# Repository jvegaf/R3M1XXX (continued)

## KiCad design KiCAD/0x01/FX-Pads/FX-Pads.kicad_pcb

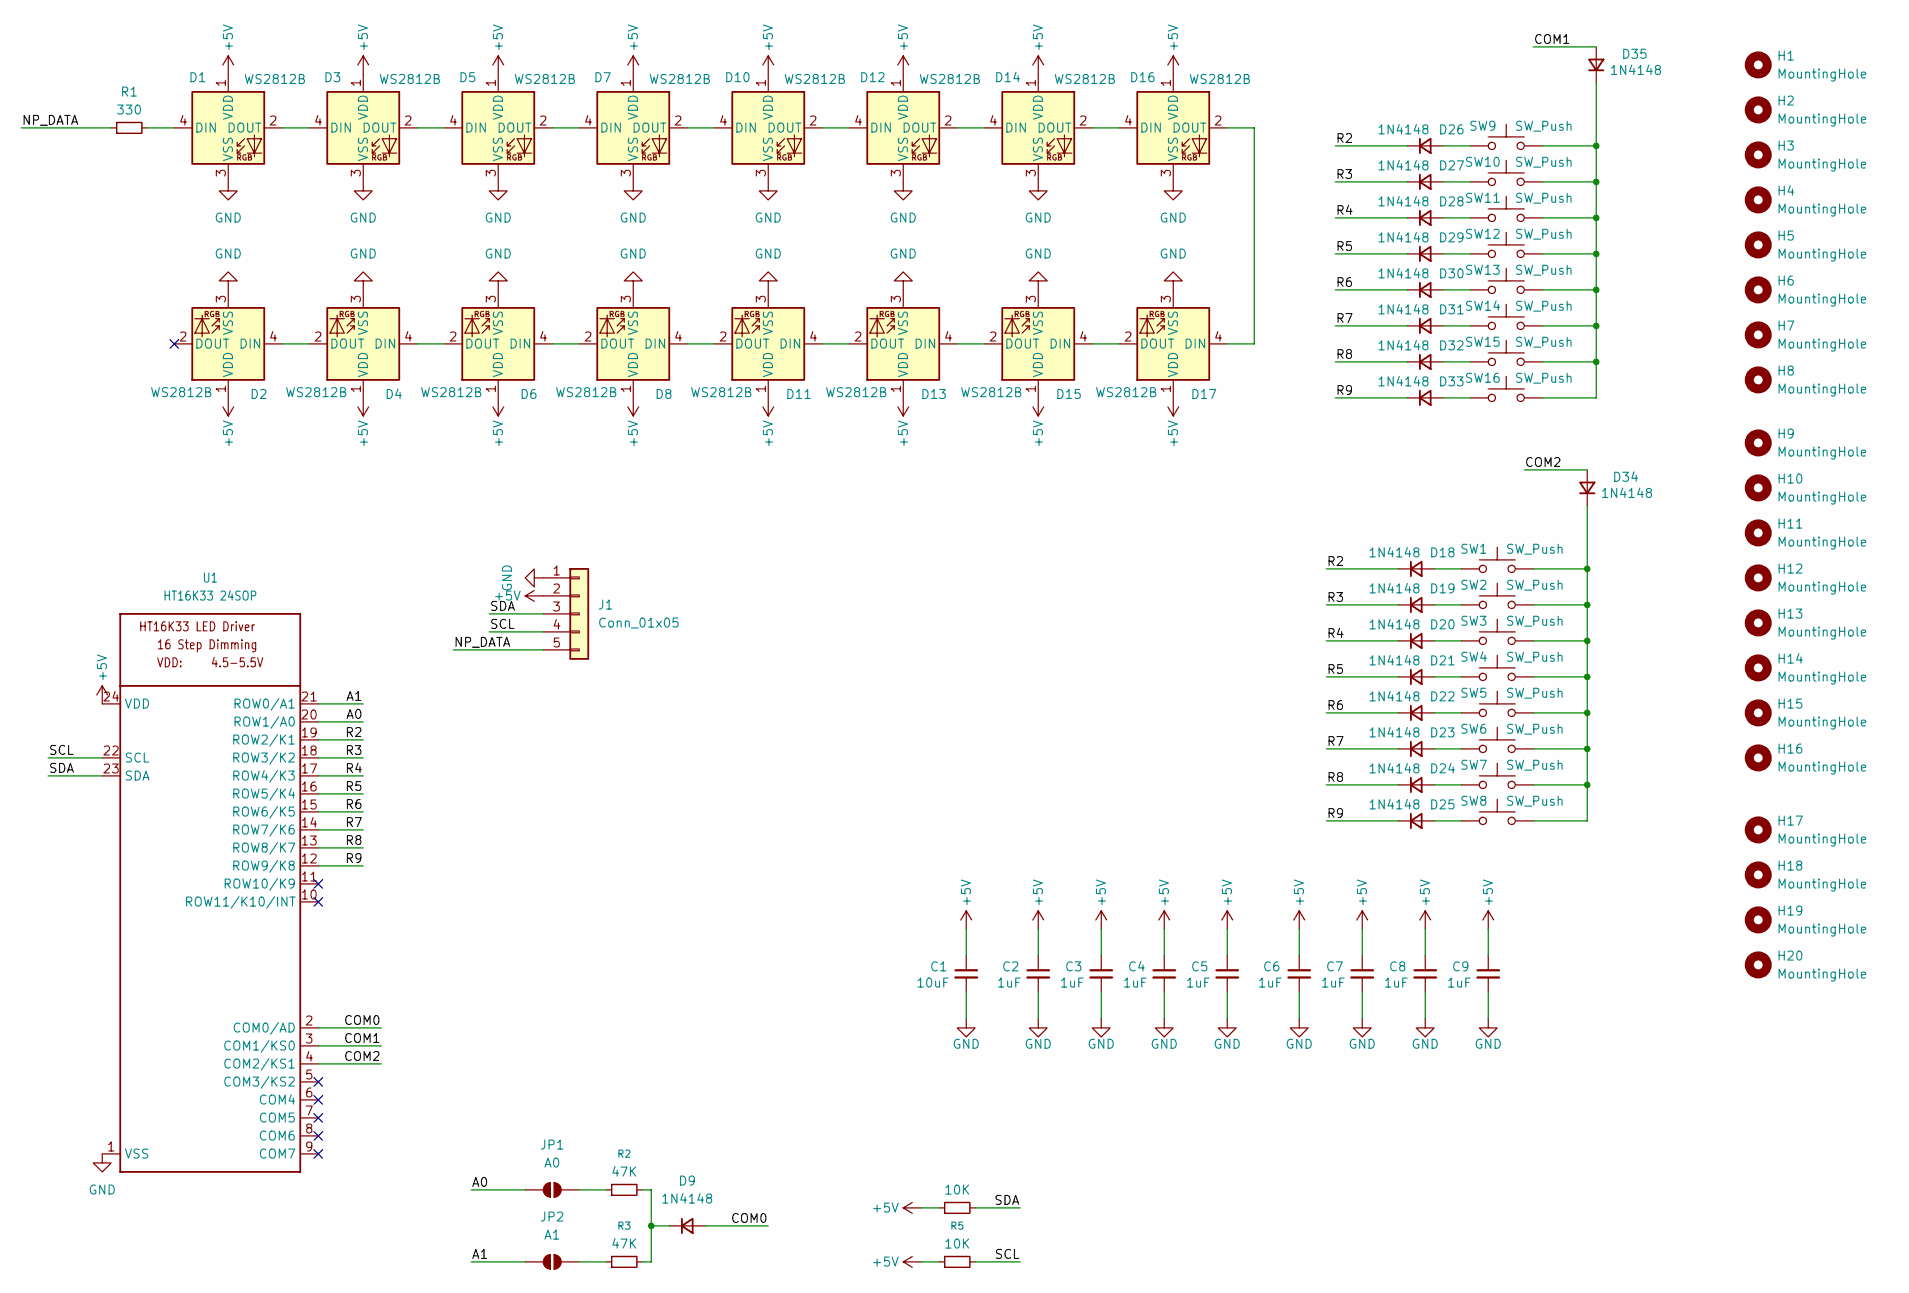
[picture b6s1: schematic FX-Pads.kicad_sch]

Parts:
C1: 10uF; C_0805_2012Metric_Pad1.18x1.45mm_HandSolder
C2, C3, C4, C5, C6, C7, C8, C9: 1uF; C_0603_1608Metric_Pad1.08x0.95mm_HandSolder
D1, D2, D3, D4, D5, D6, D7, D8, D10, D11, D12, D13, D14, D15, D16, D17: WS2812B; LED_WS2812B_PLCC4_5.0x5.0mm_P3.2mm
D9, D18, D19, D20, D21, D22, D23, D24, D25, D26, D27, D28, D29, D30, D31, D32, D33, D34, D35: 1N4148; D_SOD-123
H1, H2, H3, H4, H5, H6, H7, H8, H9, H10, H11, H12, H13, H14, H15, H16: MountingHole; MountingHole_3.2mm_M3_ISO7380
H17, H18, H19, H20: MountingHole; MountingHole_2.2mm_M2
J1: Conn_01x05; JST_PH_S5B-PH-K_1x05_P2.00mm_Horizontal
JP1: A0; SolderJumper-2_P1.3mm_Open_RoundedPad1.0x1.5mm
JP2: A1; SolderJumper-2_P1.3mm_Open_RoundedPad1.0x1.5mm
R1: 330; R_0805_2012Metric_Pad1.20x1.40mm_HandSolder
R2, R3: 47K; R_0805_2012Metric_Pad1.20x1.40mm_HandSolder
R4, R5: 10K; R_0805_2012Metric_Pad1.20x1.40mm_HandSolder
SW1, SW2, SW3, SW4, SW5, SW6, SW7, SW8, SW9, SW10, SW11, SW12, SW13, SW14, SW15, SW16: SW_Push; sw-pad
U1: HT16K33 24SOP; SOIC-24W_7.5x15.4mm_P1.27mm

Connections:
+5V: C1.1, C2.1, C3.1, C4.1, C5.1, C6.1, C7.1, C8.1, C9.1, D1.1 (VDD), D2.1 (VDD), D3.1 (VDD), D4.1 (VDD), D5.1 (VDD), D6.1 (VDD), D7.1 (VDD), D8.1 (VDD), D10.1 (VDD), D11.1 (VDD), D12.1 (VDD), D13.1 (VDD), D14.1 (VDD), D15.1 (VDD), D16.1 (VDD), D17.1 (VDD), J1.2, R4.1, R5.1, U1.24 (VDD)
/A0: JP1.1 (A), U1.20 (ROW1/A0)
/A1: JP2.1 (A), U1.21 (ROW0/A1)
/COM0: D9.2 (A), U1.2 (COM0/AD)
/COM1: D35.2 (A), U1.3 (COM1/KS0)
/COM2: D34.2 (A), U1.4 (COM2/KS1)
/NP_DATA: J1.5, R1.1
/R2: D18.1 (K), D26.1 (K), U1.19 (ROW2/K1)
/R3: D19.1 (K), D27.1 (K), U1.18 (ROW3/K2)
/R4: D20.1 (K), D28.1 (K), U1.17 (ROW4/K3)
/R5: D21.1 (K), D29.1 (K), U1.16 (ROW5/K4)
/R6: D22.1 (K), D30.1 (K), U1.15 (ROW6/K5)
/R7: D23.1 (K), D31.1 (K), U1.14 (ROW7/K6)
/R8: D24.1 (K), D32.1 (K), U1.13 (ROW8/K7)
/R9: D25.1 (K), D33.1 (K), U1.12 (ROW9/K8)
/SCL: J1.4, R5.2, U1.22 (SCL)
/SDA: J1.3, R4.2, U1.23 (SDA)
GND: C1.2, C2.2, C3.2, C4.2, C5.2, C6.2, C7.2, C8.2, C9.2, D1.3 (VSS), D2.3 (VSS), D3.3 (VSS), D4.3 (VSS), D5.3 (VSS), D6.3 (VSS), D7.3 (VSS), D8.3 (VSS), D10.3 (VSS), D11.3 (VSS), D12.3 (VSS), D13.3 (VSS), D14.3 (VSS), D15.3 (VSS), D16.3 (VSS), D17.3 (VSS), J1.1, U1.1 (VSS)
unnamed: D1.4 (DIN), R1.2
unnamed: D1.2 (DOUT), D3.4 (DIN)
unnamed: D2.4 (DIN), D4.2 (DOUT)
unnamed: D3.2 (DOUT), D5.4 (DIN)
unnamed: D4.4 (DIN), D6.2 (DOUT)
unnamed: D5.2 (DOUT), D7.4 (DIN)
unnamed: D6.4 (DIN), D8.2 (DOUT)
unnamed: D9.1 (K), R2.2, R3.2
unnamed: D7.2 (DOUT), D10.4 (DIN)
unnamed: D10.2 (DOUT), D12.4 (DIN)
unnamed: D11.4 (DIN), D13.2 (DOUT)
unnamed: D8.4 (DIN), D11.2 (DOUT)
unnamed: D12.2 (DOUT), D14.4 (DIN)
unnamed: D13.4 (DIN), D15.2 (DOUT)
unnamed: D14.2 (DOUT), D16.4 (DIN)
unnamed: D15.4 (DIN), D17.2 (DOUT)
unnamed: D16.2 (DOUT), D17.4 (DIN)
unnamed: D18.2 (A), SW1.1
unnamed: D19.2 (A), SW2.1
unnamed: D20.2 (A), SW3.1
unnamed: D21.2 (A), SW4.1
unnamed: D22.2 (A), SW5.1
unnamed: D23.2 (A), SW6.1
unnamed: D24.2 (A), SW7.1
unnamed: D25.2 (A), SW8.1
unnamed: D26.2 (A), SW9.1
unnamed: D27.2 (A), SW10.1
unnamed: D28.2 (A), SW11.1
unnamed: D29.2 (A), SW12.1
unnamed: D30.2 (A), SW13.1
unnamed: D31.2 (A), SW14.1
unnamed: D32.2 (A), SW15.1
unnamed: D33.2 (A), SW16.1
unnamed: D34.1 (K), SW1.2, SW2.2, SW3.2, SW4.2, SW5.2, SW6.2, SW7.2, SW8.2
unnamed: D35.1 (K), SW9.2, SW10.2, SW11.2, SW12.2, SW13.2, SW14.2, SW15.2, SW16.2
unnamed: JP1.2 (B), R2.1
unnamed: JP2.2 (B), R3.1

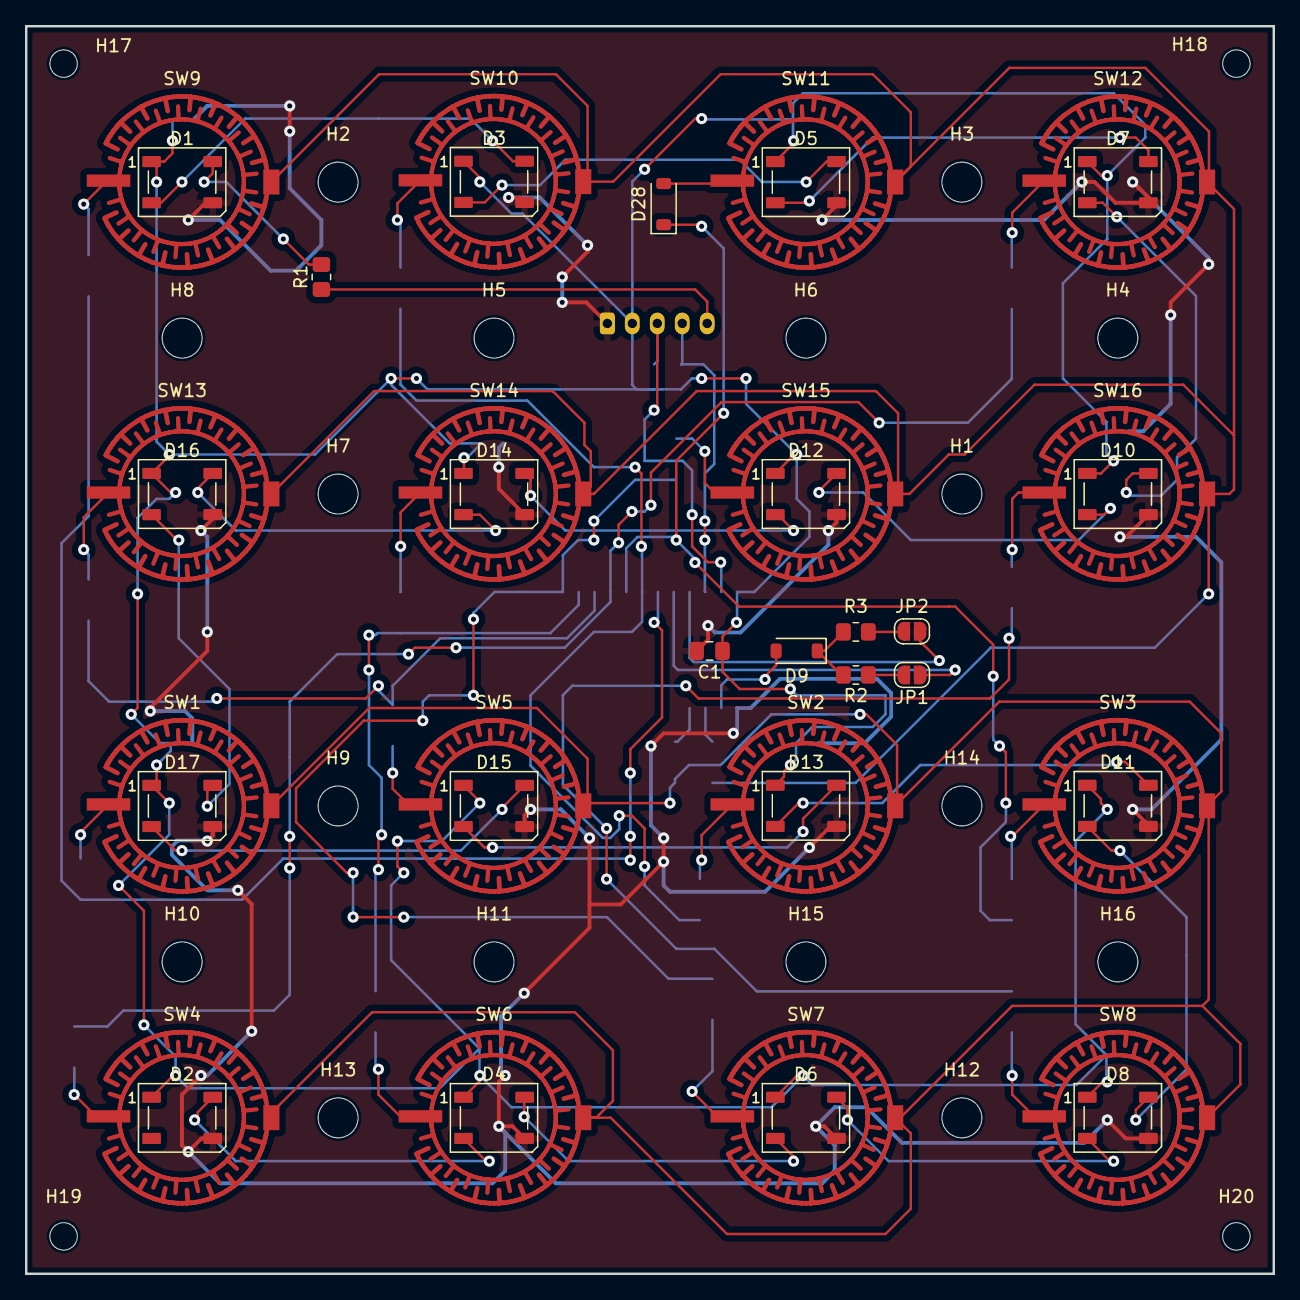
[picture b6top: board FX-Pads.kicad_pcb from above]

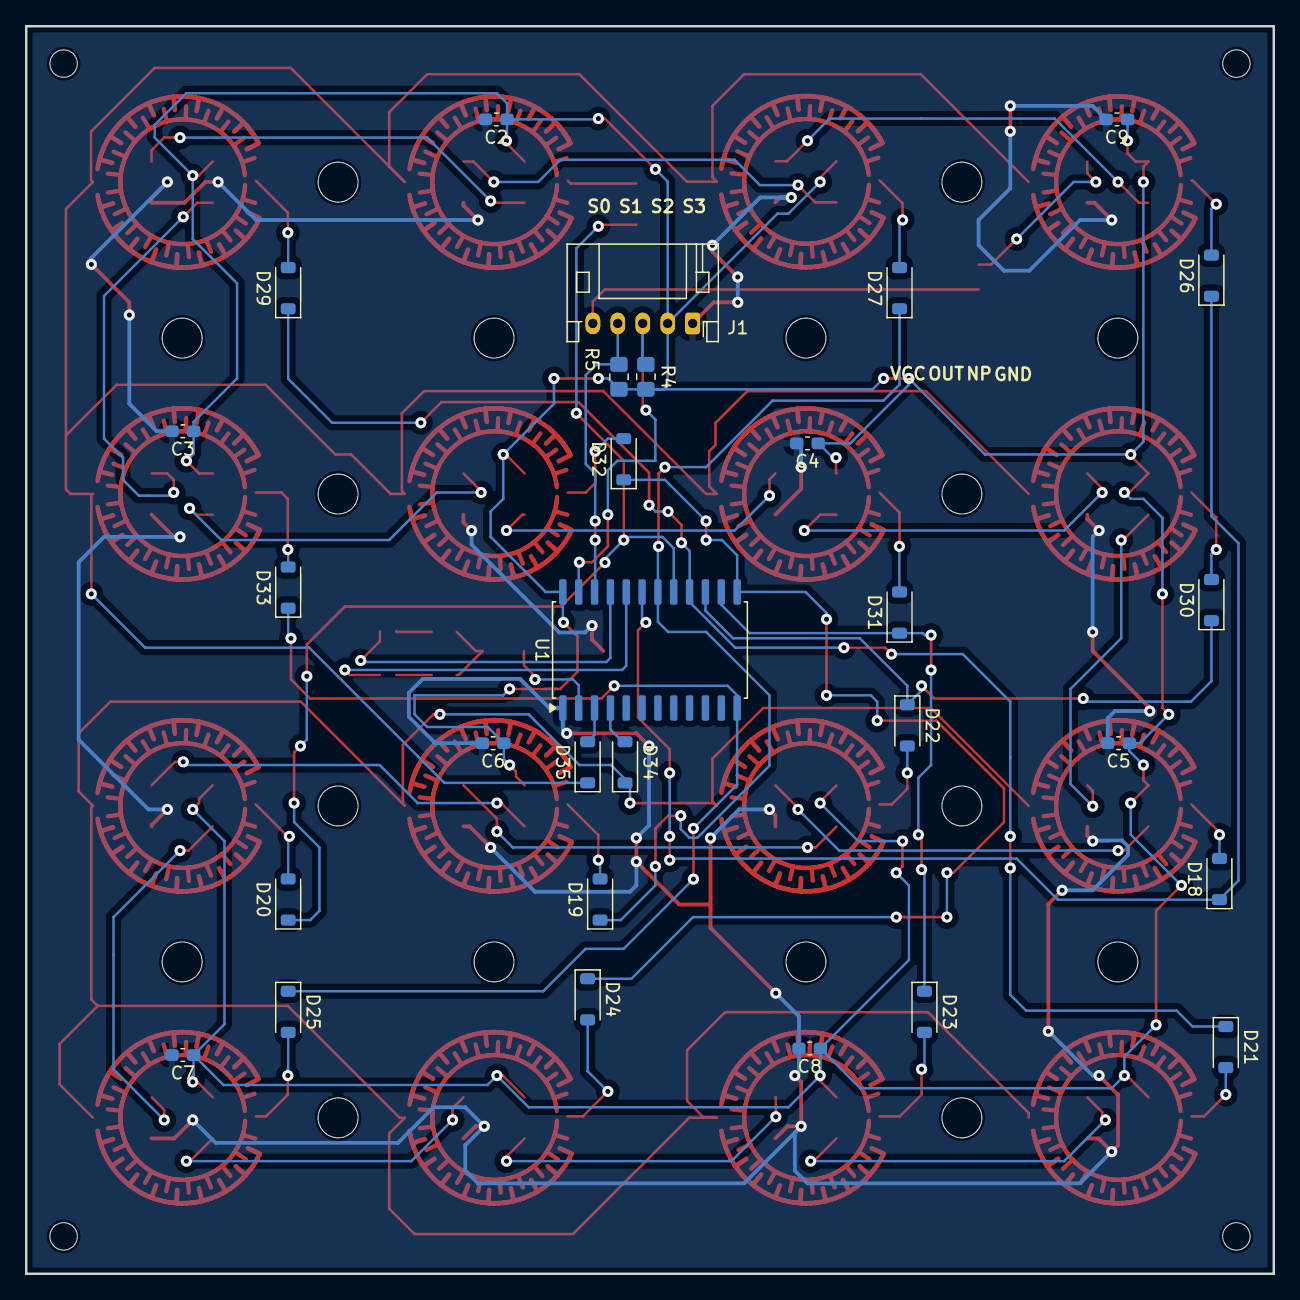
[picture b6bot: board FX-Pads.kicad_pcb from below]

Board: 2 copper layers, 100.0 x 100.0 mm, 89 parts (29 on the bottom side), 55 nets.

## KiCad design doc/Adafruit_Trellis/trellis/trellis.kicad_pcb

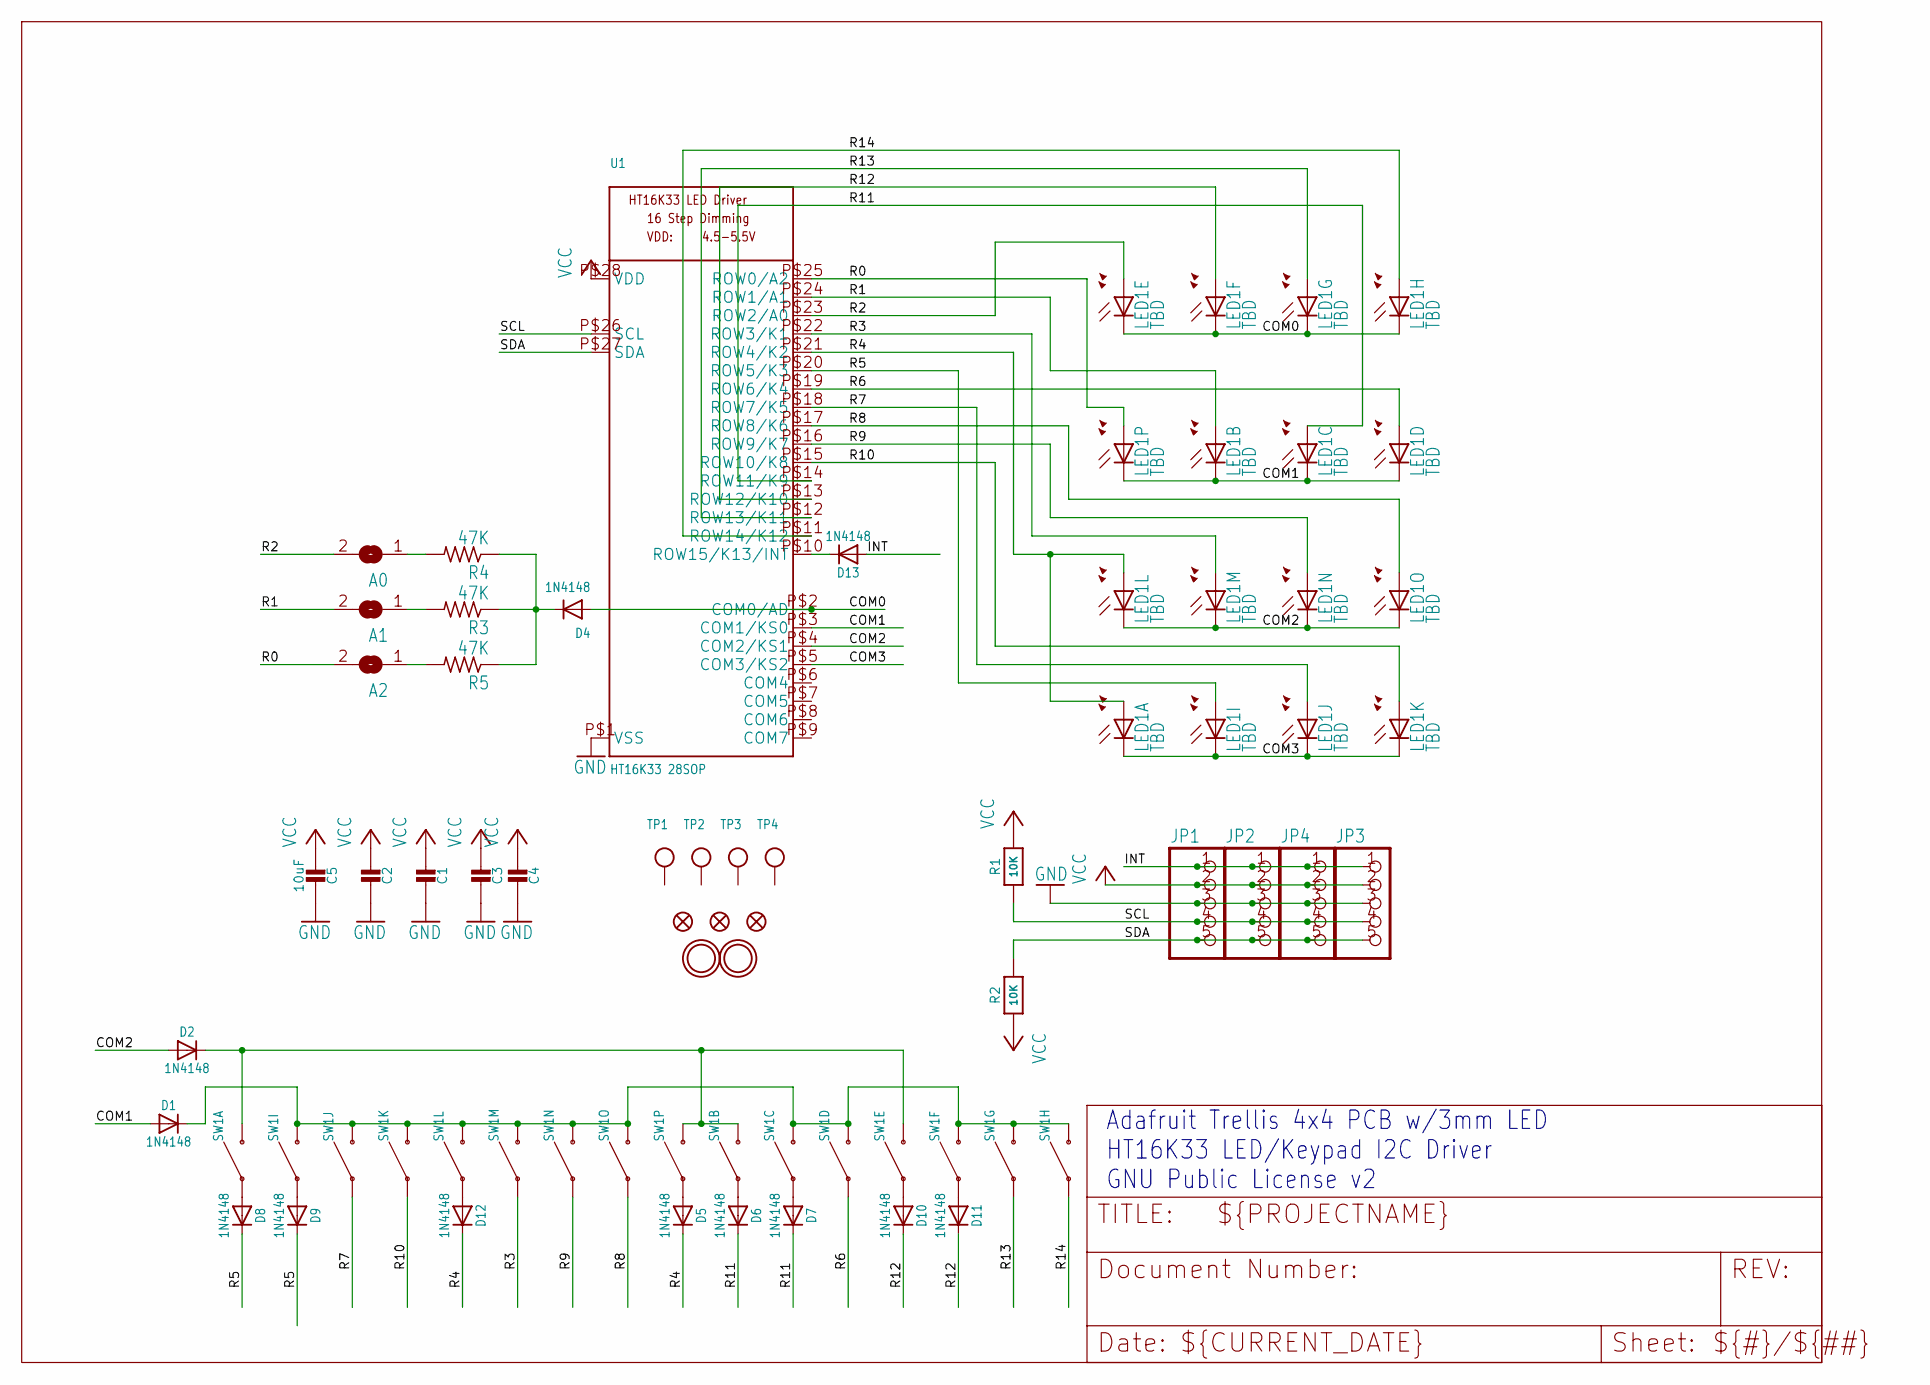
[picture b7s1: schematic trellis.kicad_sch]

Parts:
A0, A1, A2: SOLDERJUMPERREFLOW_NOPASTE; SOLDERJUMPER_REFLOW_NOPASTE
C1, C2, C3, C4: CAP_CERAMIC_0805; _0805
C5: 10uF; _0805
D1, D2, D5, D6, D7, D8, D9, D10, D11, D12, D13: 1N4148; SOD-323
D4: 1N4148; SOD-323F
FID1, FID2, FID3: FIDUCIAL""; FIDUCIAL_1MM
JP1, JP2, JP3, JP4: HEADER-1X5EDGESMT; 1X5_SMT
LED1: TBD; LED3MM-4X4GRID
R1, R2: 10K; _0805
R3, R4, R5: 47K; R0805
SW1: SWITCH-SILICON-4X4GRID-10MM-5.4MM; ELAST_PAD_SQUARE_10MM_5.4MM_4X4GRID
TP1, TP2, TP3, TP4: TESTPOINT; TESTPOINT_SMT
U1: HT16K33 28SOP; SOP28_300MIL
U$1, U$2: MOUNTINGHOLE2.5; MOUNTINGHOLE_2.5_PLATED

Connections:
COM0: D4.A, LED1.K13 (C), LED1.K14 (C), LED1.K15 (C), LED1.K16 (C), U1.P$2 (COM0/AD)
COM1: D1.A, LED1.K9 (C), LED1.K10 (C), LED1.K11 (C), LED1.K12 (C), U1.P$3 (COM1/KS0)
COM2: D2.A, LED1.K5 (C), LED1.K6 (C), LED1.K7 (C), LED1.K8 (C), U1.P$4 (COM2/KS1)
COM3: LED1.K1 (C), LED1.K2 (C), LED1.K3 (C), LED1.K4 (C), U1.P$5 (COM3/KS2)
GND: C1.1, C2.1, C3.1, C4.1, C5.1, JP1.3, JP2.3, JP3.3, JP4.3, U1.P$1 (VSS)
INT: D13.A, JP1.1, JP2.1, JP3.1, JP4.1
unnamed: D2.C, SW1.B1, SW1.B9, SW1.B10, SW1.B13
unnamed: D13.C, U1.P$10 (ROW15/K13/INT)
unnamed: D5.A, SW1.A9
unnamed: D6.A, SW1.A10
unnamed: D1.C, SW1.B2, SW1.B3, SW1.B4, SW1.B5, SW1.B6, SW1.B7, SW1.B8, SW1.B11, SW1.B12, SW1.B14, SW1.B15, SW1.B16
unnamed: D7.A, SW1.A11
unnamed: D8.A, SW1.A1
unnamed: D9.A, SW1.A2
unnamed: A2.1, R5.2
unnamed: D10.A, SW1.A13
unnamed: D11.A, SW1.A14
unnamed: D12.A, SW1.A5
unnamed: D4.C, R3.1, R4.1, R5.1
unnamed: A1.1, R3.2
unnamed: A0.1, R4.2
R0: A2.2, LED1.A9 (A), U1.P$25 (ROW0/A2)
R1: A1.2, LED1.A10 (A), U1.P$24 (ROW1/A1)
R2: A0.2, LED1.A13 (A), U1.P$23 (ROW2/A0)
R3: LED1.A6 (A), SW1.A6, U1.P$22 (ROW3/K1)
R4: D5.C, D12.C, LED1.A1 (A), LED1.A5 (A), U1.P$21 (ROW4/K2)
R5: D8.C, D9.C, LED1.A2 (A), U1.P$20 (ROW5/K3)
R6: LED1.A12 (A), SW1.A12, U1.P$19 (ROW6/K4)
R7: LED1.A3 (A), SW1.A3, U1.P$18 (ROW7/K5)
R8: LED1.A8 (A), SW1.A8, U1.P$17 (ROW8/K6)
R9: LED1.A7 (A), SW1.A7, U1.P$16 (ROW9/K7)
R10: LED1.A4 (A), SW1.A4, U1.P$15 (ROW10/K8)
R11: D6.C, D7.C, LED1.A11 (A), U1.P$14 (ROW11/K9)
R12: D10.C, D11.C, LED1.A14 (A), U1.P$13 (ROW12/K10)
R13: LED1.A15 (A), SW1.A15, U1.P$12 (ROW13/K11)
R14: LED1.A16 (A), SW1.A16, U1.P$11 (ROW14/K12)
SCL: JP1.4, JP2.4, JP3.4, JP4.4, R1.1, U1.P$26 (SCL)
SDA: JP1.5, JP2.5, JP3.5, JP4.5, R2.2, U1.P$27 (SDA)
VCC: C1.2, C2.2, C3.2, C4.2, C5.2, JP1.2, JP2.2, JP3.2, JP4.2, R1.2, R2.1, U1.P$28 (VDD)

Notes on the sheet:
Adafruit Trellis 4x4 PCB w/3mm LED HT16K33 LED/Keypad I2C Driver GNU Public License v2

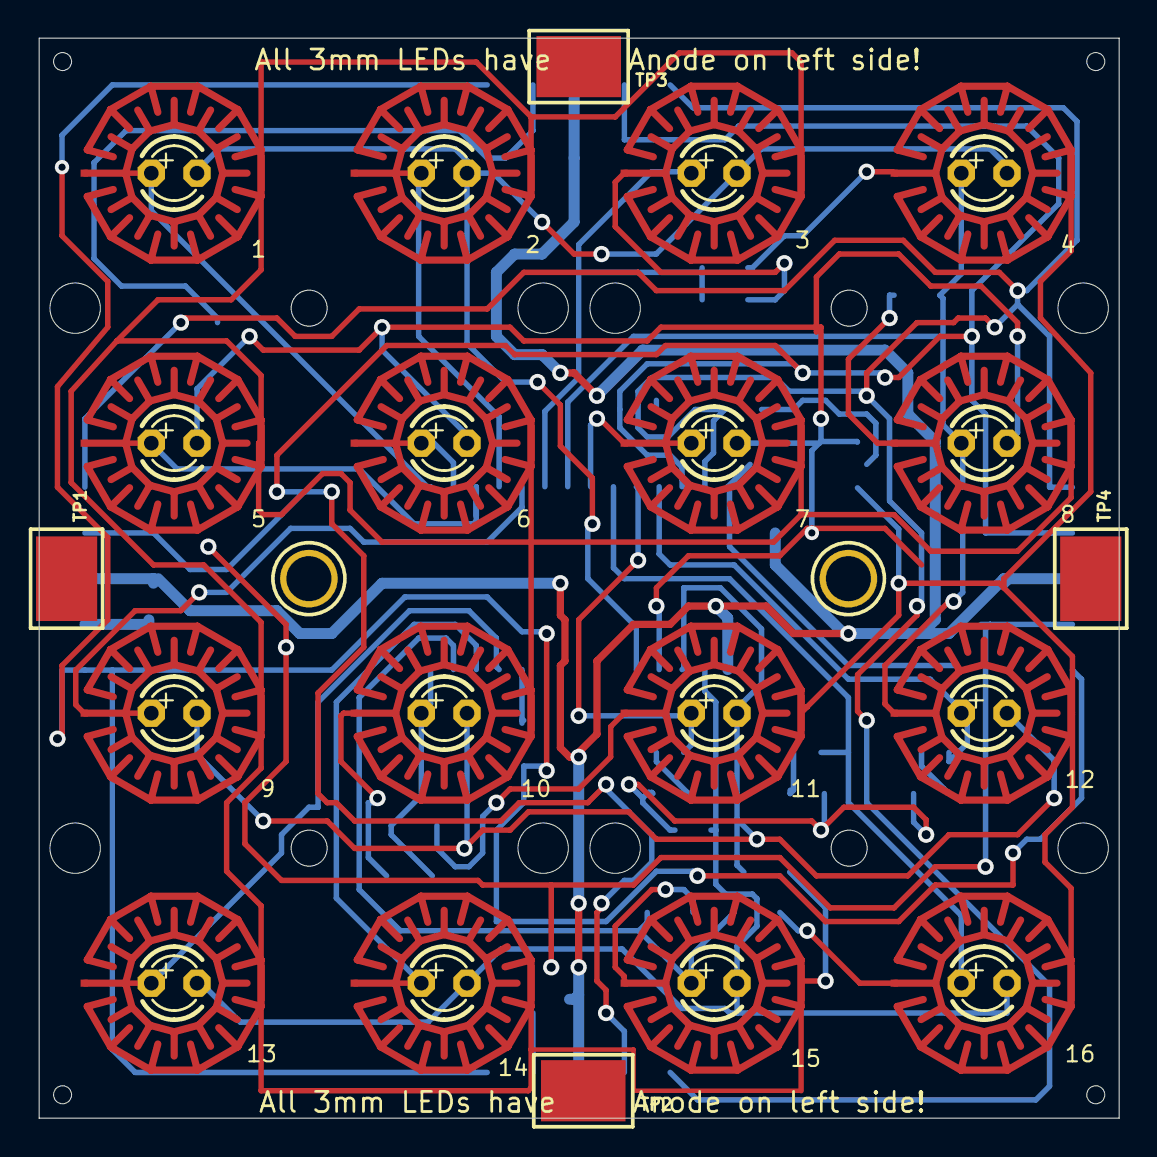
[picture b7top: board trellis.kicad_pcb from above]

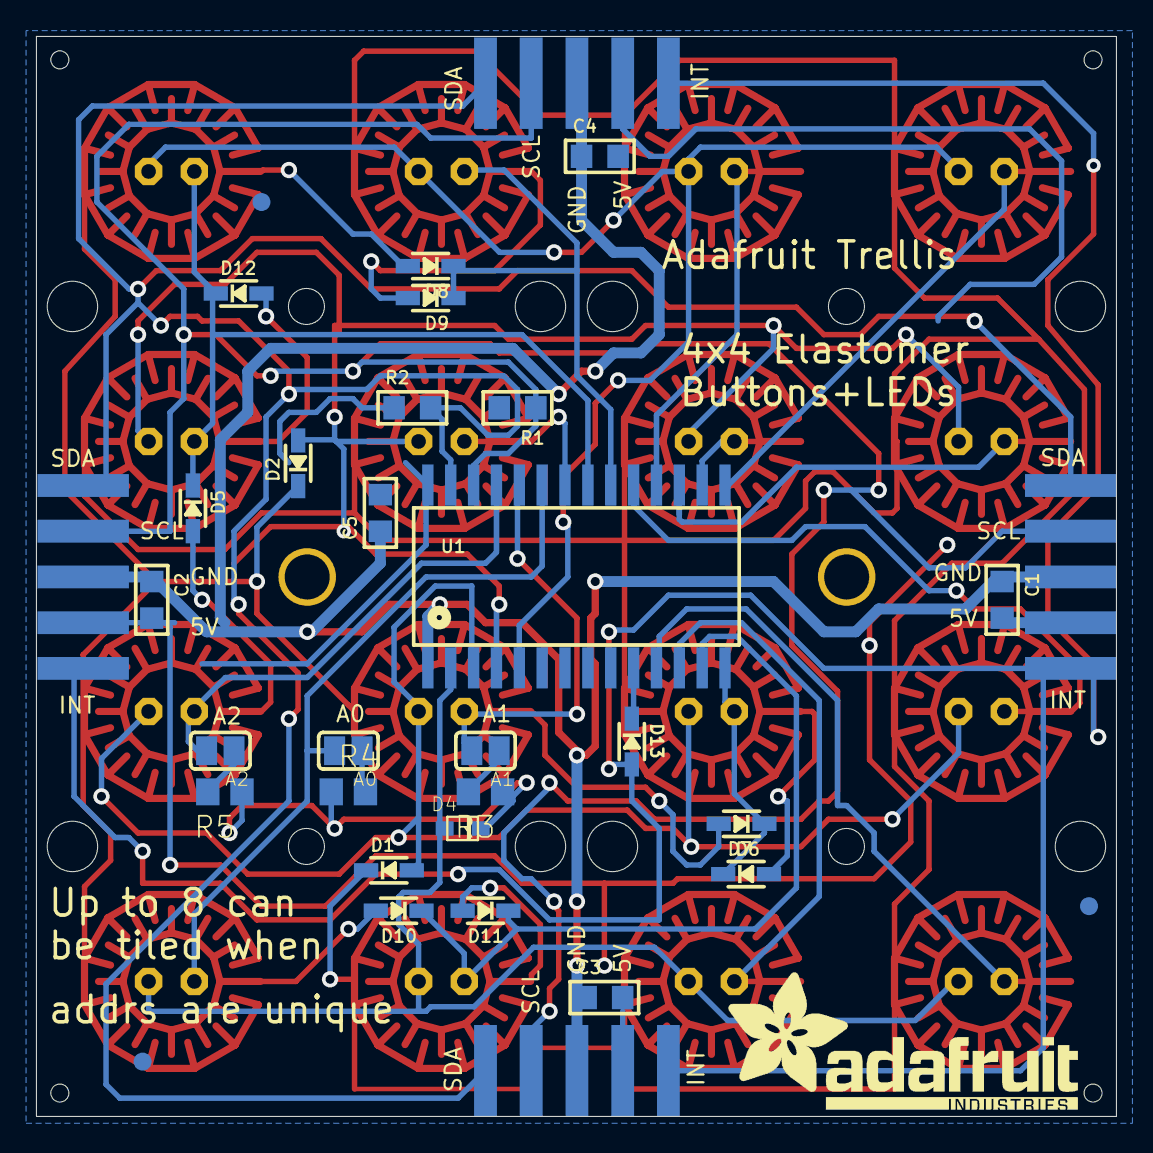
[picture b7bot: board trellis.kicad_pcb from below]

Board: 2 copper layers, 60.0 x 60.0 mm, 42 parts (34 on the bottom side), 39 nets.

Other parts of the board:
U$3: ADAFRUIT_TEXT_20MM

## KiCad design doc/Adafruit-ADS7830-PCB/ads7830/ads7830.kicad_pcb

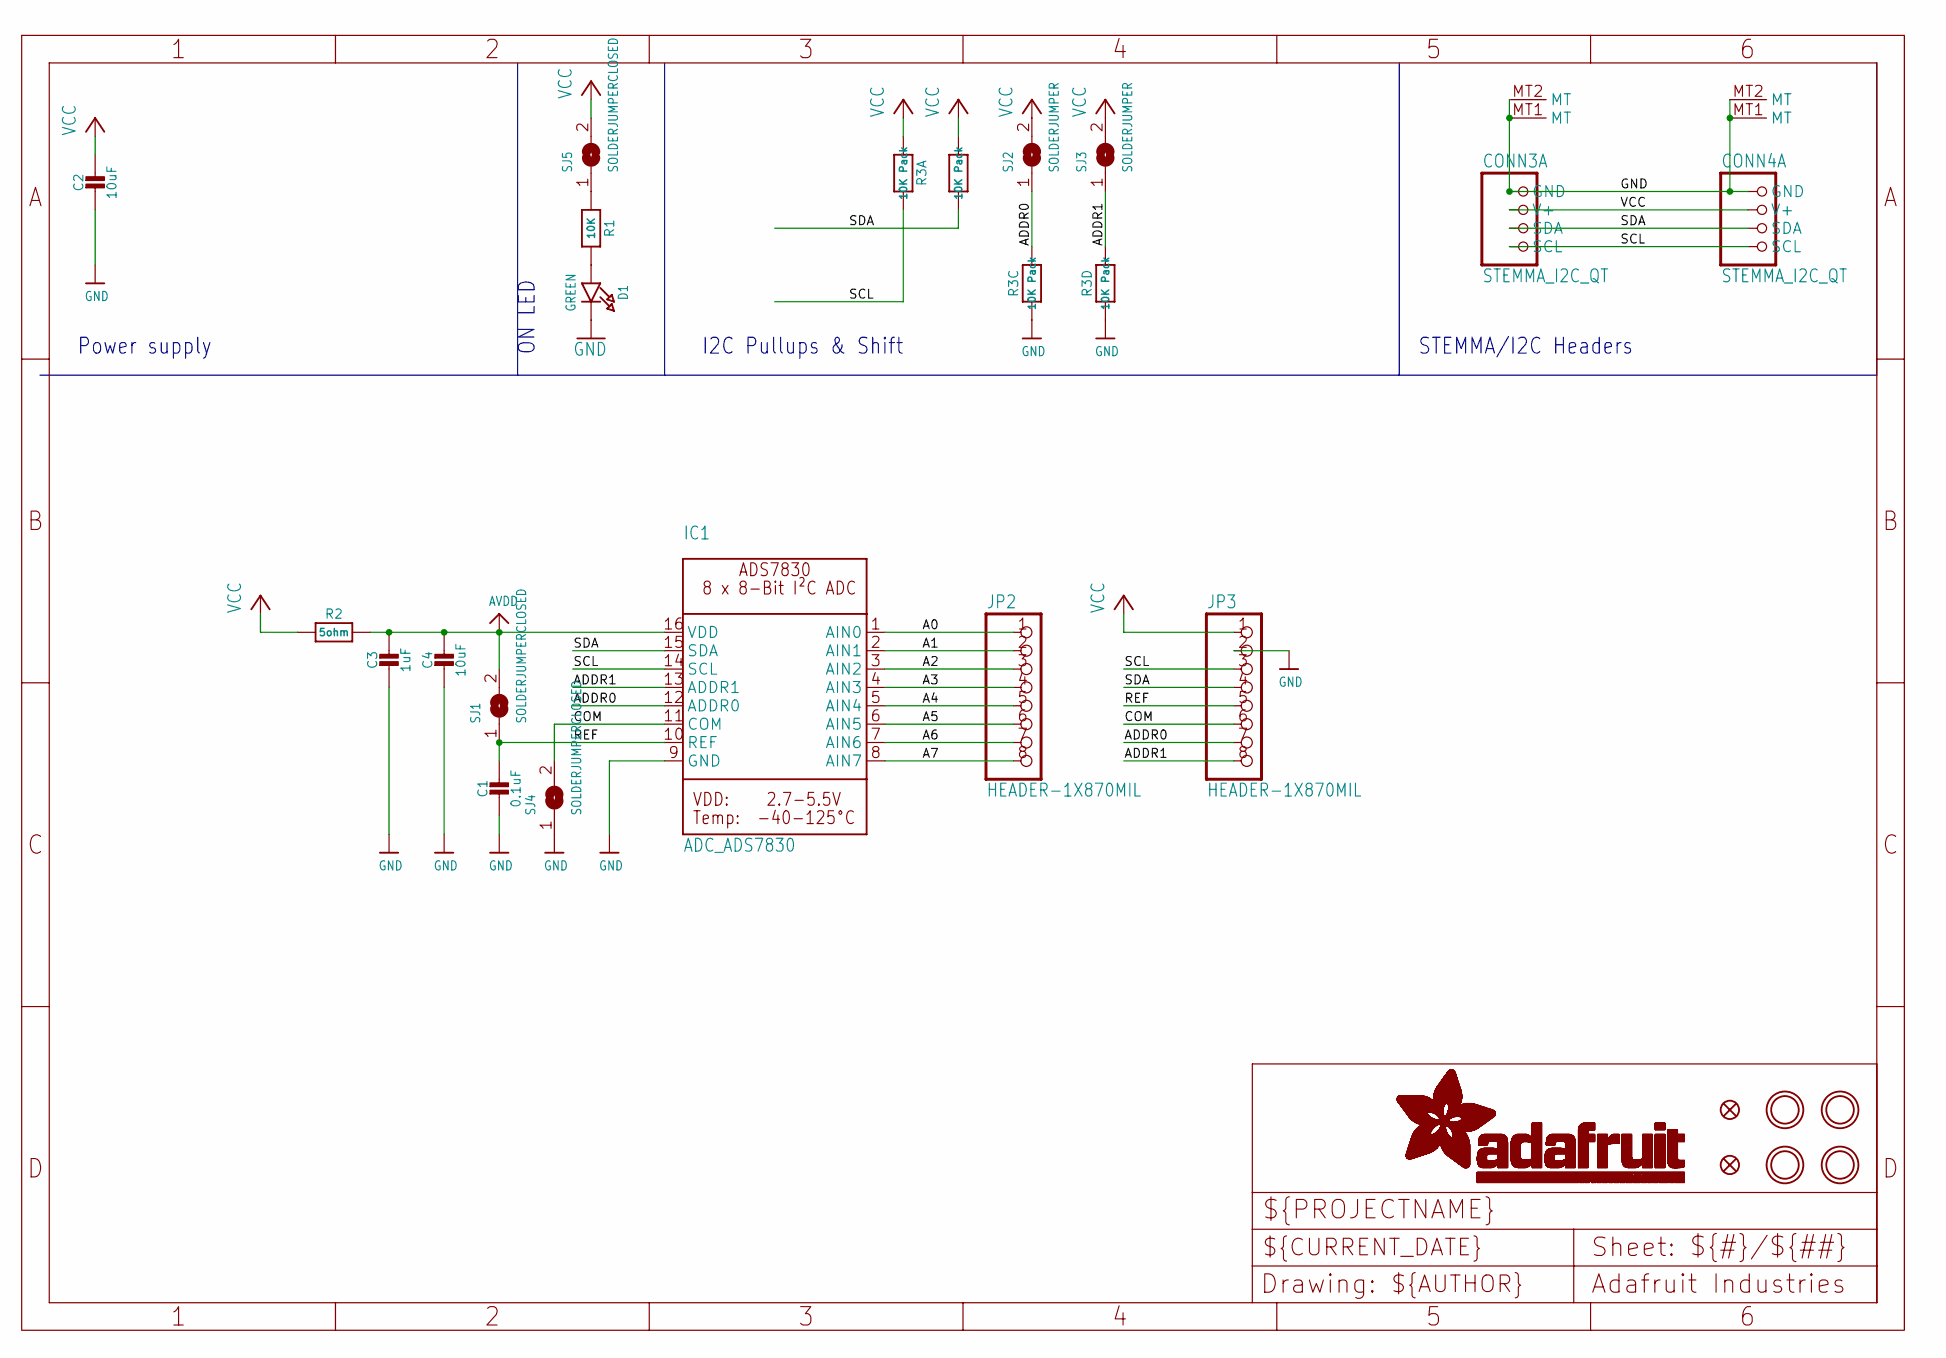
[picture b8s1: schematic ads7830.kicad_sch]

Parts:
C1: 0.1uF; 0603-NO
C2, C4: 10uF; 0805-NO
C3: 1uF; 0603-NO
CONN3, CONN4: STEMMA_I2C_QT; JST_SH4
D1: GREEN; CHIPLED_0603_NOOUTLINE
FID3, FID4: FIDUCIAL_1MM
IC1: ADC_ADS7830; TSSOP16
JP2, JP3: HEADER-1X870MIL; 1X08_ROUND_70
R1: 10K; 0603-NO
R2: 5ohm; 0603-NO
R3: 10K Pack; RESPACK_4X0603
SJ1, SJ4, SJ5: SOLDERJUMPERCLOSED; SOLDERJUMPER_CLOSEDWIRE
SJ2, SJ3: SOLDERJUMPER; SOLDERJUMPER_ARROW_NOPASTE
U$1, U$17, U$19, U$21: MOUNTINGHOLE2.5; MOUNTINGHOLE_2.5_PLATED

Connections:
A0: IC1.1 (AIN0), JP2.1
A1: IC1.2 (AIN1), JP2.2
A2: IC1.3 (AIN2), JP2.3
A3: IC1.4 (AIN3), JP2.4
A4: IC1.5 (AIN4), JP2.5
A5: IC1.6 (AIN5), JP2.6
A6: IC1.7 (AIN6), JP2.7
A7: IC1.8 (AIN7), JP2.8
ADDR0: IC1.12 (ADDR0), JP3.7, R3.6 (2), SJ2.1
ADDR1: IC1.13 (ADDR1), JP3.8, R3.5 (2), SJ3.1
AVDD: C3.1, C4.1, IC1.16 (VDD), R2.2, SJ1.2
COM: IC1.11 (COM), JP3.6, SJ4.2
GND: C1.2, C2.2, C3.2, C4.2, CONN3.1 (GND), CONN3.MT1 (MT), CONN3.MT2 (MT), CONN4.1 (GND), CONN4.MT1 (MT), CONN4.MT2 (MT), D1.C, IC1.9 (GND), JP3.2, R3.3 (1), R3.4 (1), SJ4.1
unnamed: D1.A, R1.2
unnamed: R1.1, SJ5.1
REF: C1.1, IC1.10 (REF), JP3.5, SJ1.1
SCL: CONN3.4 (SCL), CONN4.4 (SCL), IC1.14 (SCL), JP3.3, R3.8 (2)
SDA: CONN3.3 (SDA), CONN4.3 (SDA), IC1.15 (SDA), JP3.4, R3.7 (2)
VCC: C2.1, CONN3.2 (V+), CONN4.2 (V+), JP3.1, R2.1, R3.1, R3.2 (1), SJ2.2, SJ3.2, SJ5.2

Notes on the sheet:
I2C Pullups & Shift
ON LED
Power supply
STEMMA/I2C Headers

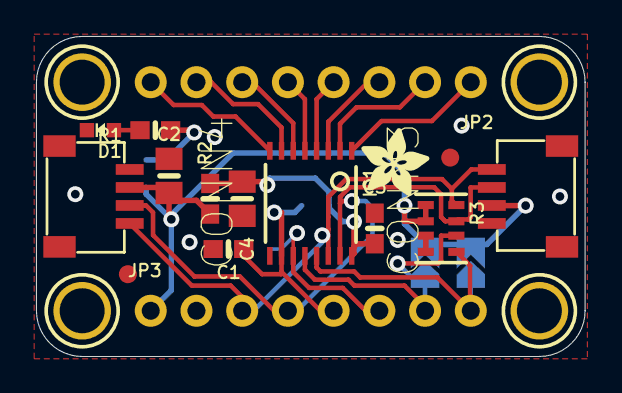
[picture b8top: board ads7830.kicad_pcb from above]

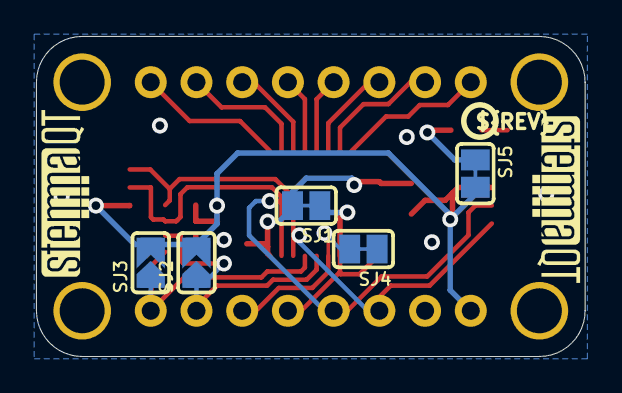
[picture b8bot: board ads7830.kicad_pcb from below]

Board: 2 copper layers, 30.5 x 17.8 mm, 54 parts (16 on the bottom side), 19 nets.

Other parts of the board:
PLABEL0: PLABEL0
PLABEL1: PLABEL1
PLABEL2: PLABEL2
PLABEL3: PLABEL3
PLABEL4: PLABEL4
PLABEL5: PLABEL5
PLABEL6: PLABEL6
PLABEL7: PLABEL7
PLABEL8: PLABEL8
PLABEL9: PLABEL9
PLABEL10: PLABEL10
PLABEL11: PLABEL11
PLABEL12: PLABEL12
PLABEL13: PLABEL13
PLABEL14: PLABEL14
PLABEL15: PLABEL15
PLABEL16: PLABEL16
PLABEL17: PLABEL17
PLABEL18: PLABEL18
PLABEL19: PLABEL19
PLABEL20: PLABEL20
PLABEL21: PLABEL21
PLABEL22: PLABEL22
PLABEL23: PLABEL23
PLABEL24: PLABEL24
PLABEL25: PLABEL25
U$22: ADAFRUIT_3.5MM
U$25: PCBFEAT-REV-040
U$30, U$31: STEMMAQT

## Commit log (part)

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2024-08-01 chore: Add KiCad library and footprints for PCB design
2024-08-02 schematic wip
2024-08-04 draw 2
2024-08-04 feat: Add PDF generation functionality
    The code changes include adding the necessary functionality to generate PDF files. This feature will allow users to generate PDF versions of their documents for easy sharing and printing.
    Note: The recent user commits and recent repository commits do not provide any relevant information for generating the commit message.
2024-08-04 feat: Add PDF generation functionality
2024-08-07 M01 & X01
2024-08-08 M01 fixes
2024-08-09 pots
2024-08-09 linear pot
2024-08-12 chore: Update KiCAD gerber and drill files
    The code changes include updating the KiCAD gerber and drill files in the M01 and X01 directories. These updates ensure that the latest versions of the files are included in the repository.
    Note: The recent user commits and recent repository commits do not provide any relevant information for generating the commit message.
2024-08-13 chore: Update KiCAD gerber and drill files
2024-08-14 fx pots
2024-08-18 M01 global vu nc programs
2024-08-18 X01 fx pots nc programs
2024-08-19 ncc progs
2024-08-19 encoders mill
2024-08-19 deck btns
2024-08-20 deck btns fixes
2024-08-23 ht16k33 deck btns
2024-08-25 dck btns
2024-08-25 drawing
2024-08-25 pots rfx
2024-08-25 fx-bundle finished
2024-08-25 ignore backups
2024-08-26 gitignore
2024-08-26 ignore update
2024-08-30 schematic pdf
2024-09-02 ht16k33 arduino code
2024-09-02 gerbers & nc programs
2024-09-02 deck bundle
2024-09-02 pico st7789
2024-09-04 lcd encoders nc programs
2024-09-04 pico 7789 bis
2024-09-07 fix lcd encoders
2024-09-08 encoders
2024-09-08 nc programs
2024-09-09 fixes
2024-09-11 nc fixes
2024-09-15 clangd
2024-09-16 ili9340 && sh1106 displays
2024-09-19 ESP32-DevKit-V1-Pinout-Diagram-r0.1-CIRCUITSTATE-Electronics-2
2024-09-19 Code
2024-09-21 micropython
2024-09-21 esp32
2024-09-22 7789
2024-09-27 lcd encoders
2024-09-30 micropython i2c display
2024-10-01 ht16k33
2025-02-11 use 74hc165d with rotary encoders
2025-02-11 gerbers
2025-02-12 cpp hello world rp2040
2025-02-16 re-routing encoders pcb
2025-02-17 wiring encoders
2025-02-27 update drawings
2025-02-27 eqboard
2025-02-28 tm1637
2025-03-12 pads
2025-03-12 fx pads
2025-03-14 fx pads gerbers
2025-04-05 update ignore
2025-04-19 encoders lcd finished
2025-05-03 chore: rename encoder_tool_test to encoder_i2c_test
    The directory `encoder_tool_test` has been renamed to `encoder_i2c_test`
    to better reflect its purpose. This includes updates to associated
    files such as `.ccls`, `.gitignore`, and `.vscode/extensions.json`.
2025-05-03 update i
2025-05-10 Add symbol library table for LCD and HT16K33 components
    - Created a new symbol library table file for the project.
    - Added entries for the "0x01-Library" and "ht16k33_sop28" libraries with their respective URIs.
2025-05-10 change i2c adresss
2025-05-10 encoder i2c
2025-05-12 feat(encoder): add I2C encoder implementation
    Introduce a new I2C encoder implementation with initialization, value
    retrieval, and button press detection. Includes Encoder class with
    methods for setting and getting values, and checking button state.
    BREAKING CHANGE: Updated encoder address and initialization parameters
    in main.cpp. Ensure compatibility with the new encoder setup.
2025-05-15 feat(encoder): update encoder_set parameters in main.cpp
    Updated the encoder_set function call in src/main.cpp to use a range of
    -50 to 50 instead of 0 to 1. This change ensures better testing of the
    encoder's functionality with a wider range of values.
    Also added a new entry for Encoder.cpp in compile_commands.json to
    support proper compilation and linking of the Encoder source file.
2025-05-16 demo lcd ht16k33
2025-05-17 feat(circuitpy): add I2C encoder and NeoPixel examples
    - Added I2C encoder example with functions for reading, writing, and
    configuration.
    - Included NeoPixel example demonstrating color chase and rainbow cycle
    effects.
    - Added I2C scan utility for detecting connected devices.
    - Configured VSCode settings for CircuitPython development.
2025-05-17 feat: support multiple encoders in I2C test
    Refactor the code to handle multiple encoders instead of a single one.
    - Replace single encoder instance with an array of encoders.
    - Add arrays to track encoder values and pressed states.
    - Update setup and loop functions to iterate over all encoders.
    This change enables testing of up to three encoders simultaneously.
2025-05-17 feat(platformio): add ESP32-C3 Supermini environment configuration
2025-05-18 lcd encoder cpp
2025-05-21 encoders class
2025-05-21 Refactor Encoder and Encoders classes for improved memory management and functionality
    - Updated Encoder constructor to accept TwoWire pointer instead of reference.
    - Modified Encoders class to dynamically allocate Encoder objects and manage their lifecycle.
    - Replaced raw array usage with dynamic arrays for values and pressed states.
    - Implemented checkState method in Encoders to handle encoder state checking and value updates.
    - Simplified main loop to utilize Encoders class for state checking instead of individual encoders.
2025-05-21 feat(encoders): enhance state management and initialization for encoders
2025-05-21 feat: add initial project structure and configuration files for LCD test project
2025-05-25 demobox ht16k33 nc files
2025-05-27 demobox fixes
2025-06-03 refactor demobox
2025-06-05 updates demo
2025-08-13 Refactor code structure for improved readability and maintainability
2025-08-13 Update README.md for HT16K33 Dual Display Utility: enhance project description, clarify functionalities, and improve command list formatting.
2025-08-13 lcd encoders with ht16k33
2025-08-13 step model
2025-08-13 fx-pots
2025-08-15 pads_demo
2025-08-18 fx pots routing
2025-08-18 esp32 c3
2025-08-18 esp32 c3 test
2025-08-20 esp32 c3 test fixes
2025-08-20 routing fx pots
2025-08-21 demobox nc
2025-08-24 feat: add Copilot instructions and tech stack docs
    Add initial Copilot guidance in .github/copilot/copilot-instructions.md
    and
    tech-stack.md for PlatformIO/ESP32-Arduino project. Include .gitignore
    for
    PlatformIO and VSCode artifacts. Prepare for consistent code generation
    and
2025-08-25 feat(tm1638): add segment/digit calibration & diagnostics
    - Added interactive calibration for segment (K) and digit (G) mapping
    to support custom TM1638 layouts.
    - Implemented raw segment sweep (T) and display toggle (x) for
    diagnostics.
    - Improved startup banner and serial handling for ESP32-C3 USB CDC.
    - Changed clear logic to use setRaw16 for consistency.
2025-08-25 fxpots
2025-08-29 fx pads step model
2025-08-29 fx pads case
2025-09-04 docs: migrate copilot instructions to esp32-c3
    replace pico/rp2040 guidelines with esp32-c3 (arduino, c++11) standards.
    define code style, versioning, and architecture for new platform.
2025-09-06 pots refactor
2025-09-06 finished fx-pots & encoders-lcd
2025-09-17 led matrix test code
2025-09-17 step models
2025-10-03 demobox
2025-10-10 fx-pads routing
2025-10-10 pads routing
2025-10-24 dock freecad model
2025-10-25 i2c discover
2025-11-06 Refactor HT16K33 test code: Enhance functionality and user experience
    - Updated platform configuration in platformio.ini for better compatibility.
    - Revamped main.cpp to provide a comprehensive diagnostic tool for HT16K33 LED matrix and keyboard.
    - Introduced an interactive menu system for selecting various LED and keyboard tests.
    - Added detailed documentation and comments throughout the code for clarity.
    - Implemented multiple LED test patterns and improved key mapping display.
    - Enhanced user feedback with structured output and error handling.
2025-11-09 ADS7830 test
2025-11-25 mpy ht16k33
2025-11-25 arduino pro micro testing
2025-11-29 Corrige direcciones I2C para los encoders y dispositivos de visualización
2025-11-29 Añade Makefile para la gestión del proyecto en PlatformIO
2025-11-29 Actualiza la herramienta utilizada en los agentes de planificación y generación de documentación a 'search/codebase'
2025-11-29 case
2025-12-01 firmware exported to new repository
2025-12-01 feat: OxO1 case 3d model
2025-12-05 upgrade ignore
2025-12-07 fx-pots refactoring WIP
2025-12-09 fxpots wip
2025-12-15 pre firm
2025-12-24 rp2040 zero
2026-01-05 xone
2026-02-11 pots problem
2026-02-13 pots fixed
2026-02-21 controller 2040 zero
2026-02-21 code discover py
2026-02-26 fx_pots_test
2026-03-17 fx_pads
2026-03-21 pads read keys
2026-03-23 pads midi
2026-03-29 pads rp2040
2026-03-30 0x1F slider pcb
2026-04-03 soic adapter
